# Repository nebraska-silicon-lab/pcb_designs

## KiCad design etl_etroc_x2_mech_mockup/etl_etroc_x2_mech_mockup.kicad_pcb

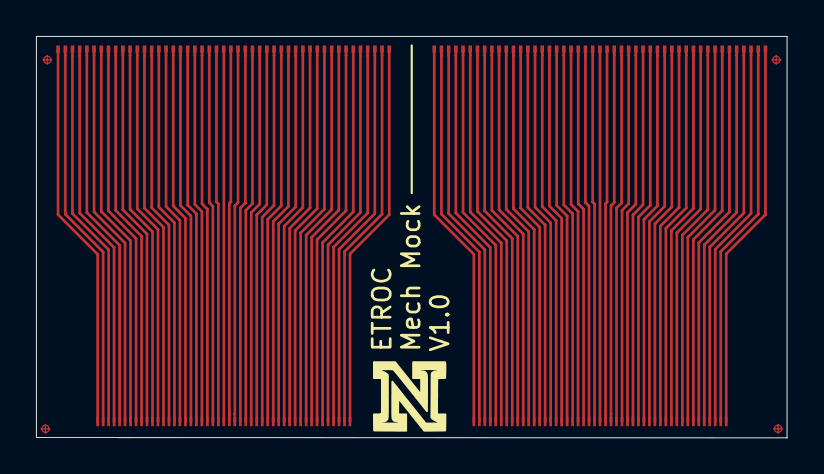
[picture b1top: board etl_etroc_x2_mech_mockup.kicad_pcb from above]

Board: 2 copper layers, 41.7 x 22.3 mm, 4 parts (0 on the bottom side), 94 nets.

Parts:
J1, J2: Conn_2Rows-47Pins; etroc_mockup_wirebond_pads
J3, J4: Conn_2Rows-47Pins; ETROC

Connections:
/A1: J1.1, J3.1
/A2: J1.2, J3.2
/A3: J1.3, J3.3
/A4: J1.4, J3.4
/A5: J1.5, J3.5
/A6: J1.6, J3.6
/A7: J1.7, J3.7
/A8: J1.8, J3.8
/A9: J1.9, J3.9
/A10: J1.10, J3.10
/A11: J1.11, J3.11
/A12: J1.12, J3.12
/A13: J1.13, J3.13
/A14: J1.14, J3.14
/A15: J1.15, J3.15
/A16: J1.16, J3.16
/A17: J1.17, J3.17
/A18: J1.18, J3.18
/A19: J1.19, J3.19
/A20: J1.20, J3.20
/A21: J1.21, J3.21
/A22: J1.22, J3.22
/A23: J1.23, J3.23
/A24: J1.24, J3.24
/A25: J1.25, J3.25
/A26: J1.26, J3.26
/A27: J1.27, J3.27
/A28: J1.28, J3.28
/A29: J1.29, J3.29
/A30: J1.30, J3.30
/A31: J1.31, J3.31
/A32: J1.32, J3.32
/A33: J1.33, J3.33
/A34: J1.34, J3.34
/A35: J1.35, J3.35
/A36: J1.36, J3.36
/A37: J1.37, J3.37
/A38: J1.38, J3.38
/A39: J1.39, J3.39
/A40: J1.40, J3.40
/A41: J1.41, J3.41
/A42: J1.42, J3.42
/A43: J1.43, J3.43
/A44: J1.44, J3.44
/A45: J1.45, J3.45
/A46: J1.46, J3.46
/A47: J1.47, J3.47
/B1: J2.1, J4.1
/B2: J2.2, J4.2
/B3: J2.3, J4.3
/B4: J2.4, J4.4
/B5: J2.5, J4.5
/B6: J2.6, J4.6
/B7: J2.7, J4.7
/B8: J2.8, J4.8
/B9: J2.9, J4.9
/B10: J2.10, J4.10
/B11: J2.11, J4.11
/B12: J2.12, J4.12
/B13: J2.13, J4.13
/B14: J2.14, J4.14
/B15: J2.15, J4.15
/B16: J2.16, J4.16
/B17: J2.17, J4.17
/B18: J2.18, J4.18
/B19: J2.19, J4.19
/B20: J2.20, J4.20
/B21: J2.21, J4.21
/B22: J2.22, J4.22
/B23: J2.23, J4.23
/B24: J2.24, J4.24
/B25: J2.25, J4.25
/B26: J2.26, J4.26
/B27: J2.27, J4.27
/B28: J2.28, J4.28
/B29: J2.29, J4.29
/B30: J2.30, J4.30
/B31: J2.31, J4.31
/B32: J2.32, J4.32
/B33: J2.33, J4.33
/B34: J2.34, J4.34
/B35: J2.35, J4.35
/B36: J2.36, J4.36
/B37: J2.37, J4.37
/B38: J2.38, J4.38
/B39: J2.39, J4.39
/B40: J2.40, J4.40
/B41: J2.41, J4.41
/B42: J2.42, J4.42
/B43: J2.43, J4.43
/B44: J2.44, J4.44
/B45: J2.45, J4.45
/B46: J2.46, J4.46
/B47: J2.47, J4.47

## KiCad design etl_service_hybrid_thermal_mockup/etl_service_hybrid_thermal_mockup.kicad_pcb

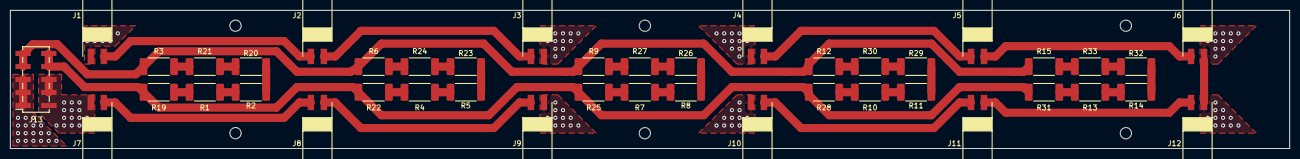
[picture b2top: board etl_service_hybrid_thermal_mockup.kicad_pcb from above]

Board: 4 copper layers, 250.0 x 27.0 mm, 43 parts (0 on the bottom side), 37 nets.

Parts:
J1, J2, J3, J4, J5, J6, J7, J8, J9, J10, J11, J12: Conn_01x02_Male; GEC02SBSN-M89
J13: Conn_02x05_Odd_Even; PinSocket_2x05_P2.54mm_Vertical_SMD
R1, R2, R3, R4, R5, R6, R7, R8, R9, R10, R11, R12, R13, R14, R15, R19, R20, R21, R22, R23, R24, R25, R26, R27, R28, R29, R30, R31, R32, R33: 226; R_2512_6332Metric_Pad1.52x3.35mm_HandSolder

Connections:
/MOD_NEG: J3.2, J6.2, J9.1, J12.1, J13.1, J13.3, J13.5
/MOD_POS: J1.1, J4.1, J7.2, J10.2, J13.2, J13.4, J13.6
/SH_NEG: J13.7, J13.9, R3.2, R6.2, R9.2, R12.2, R15.2
/SH_POS: J13.8, J13.10, R19.1, R22.1, R25.1, R28.1, R31.1
unnamed: J1.2, J2.1
unnamed: J2.2, J3.1
unnamed: J4.2, J5.1
unnamed: J5.2, J6.1
unnamed: J7.1, J8.2
unnamed: J8.1, J9.2
unnamed: J10.1, J11.2
unnamed: J11.1, J12.2
unnamed: R1.1, R19.2
unnamed: R1.2, R2.2
unnamed: R2.1, R20.2
unnamed: R4.2, R5.2
unnamed: R7.2, R8.2
unnamed: R10.1, R28.2
unnamed: R10.2, R11.2
unnamed: R11.1, R29.2
unnamed: R12.1, R30.2
unnamed: R13.1, R31.2
unnamed: R13.2, R14.2
unnamed: R14.1, R32.2
unnamed: R15.1, R33.2
unnamed: R20.1, R21.1
unnamed: R3.1, R21.2
unnamed: R4.1, R22.2
unnamed: R23.1, R24.1
unnamed: R5.1, R23.2
unnamed: R6.1, R24.2
unnamed: R7.1, R25.2
unnamed: R26.1, R27.1
unnamed: R8.1, R26.2
unnamed: R9.1, R27.2
unnamed: R29.1, R30.1
unnamed: R32.1, R33.1
